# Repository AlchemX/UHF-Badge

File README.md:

# UHF-Badge
Credit-Card sized Schottky diode RF detector with 2 indicator LEDs and PCB antenna

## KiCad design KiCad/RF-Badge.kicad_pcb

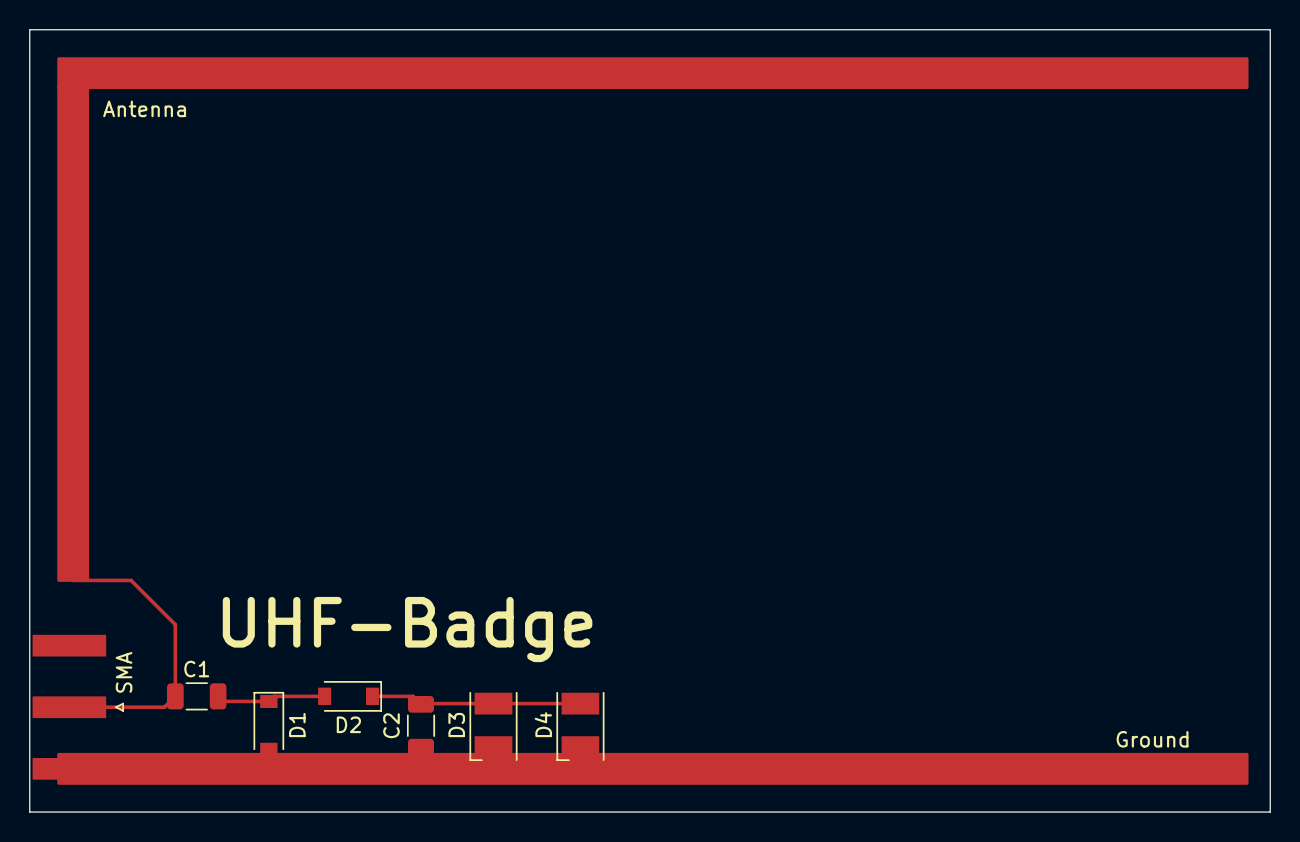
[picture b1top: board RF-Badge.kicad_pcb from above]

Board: 2 copper layers, 85.6 x 54.0 mm, 7 parts (0 on the bottom side), 4 nets.

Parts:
C1: 100pF; C_1206_3216Metric
C2: 1uF; C_1206_3216Metric
D1, D2: MMSD701T1G; D_SOD-123
D3: LTST-T680KSWT; LED_PLCC-2
D4: LTST-T680UBWT; LED_PLCC-2
SMA: Conn_Coaxial; SMA_Amphenol_132289_EdgeMount

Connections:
Earth: C2.2, D1.2 (A), D3.1 (K), D4.1 (K), SMA.2 (Ext)
unnamed: C1.1, SMA.1 (In)
unnamed: C1.2, D1.1 (K), D2.2 (A)
unnamed: C2.1, D2.1 (K), D3.2 (A), D4.2 (A)

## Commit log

2022-10-23 Create empty
